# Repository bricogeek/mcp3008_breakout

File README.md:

MCP3008 Breakout Board
================

This MCP3008 breakout board will add 8 channels of 10-bit analog input to your microcontroller or microcomputer project and uses SPI so only 4 pins are required.

[   
*MCP3008 Breakout Board (BGK-0001)*](http://tienda.bricogeek.com/bricogeek/678-conversor-adc-8-bits-mcp3008.html)

License Information
-------------------
The hardware is released under [Creative Commons ShareAlike 4.0 International](https://creativecommons.org/licenses/by-sa/4.0/).

Distributed as-is; no warranty is given.

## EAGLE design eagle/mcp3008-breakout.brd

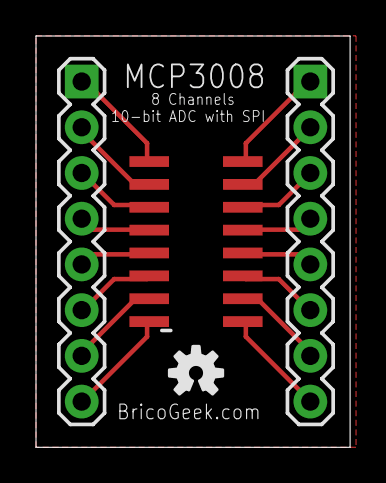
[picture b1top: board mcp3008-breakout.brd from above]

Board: 2 copper layers, 17.4 x 22.9 mm, 4 parts (0 on the bottom side), 15 nets.

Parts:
JP1, JP2: 1X08
U1: MCP3008; SOIC16N
U$2: OSHW-LOGO-S

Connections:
CH0: JP1.1, U1.1
CH1: JP1.2, U1.2
CH2: JP1.3, U1.3
CH3: JP1.4, U1.4
CH4: JP1.5, U1.5
CH5: JP1.6, U1.6
CH6: JP1.7, U1.7
CH7: JP1.8, U1.8
CLK: JP2.4, U1.13
CS: JP2.7, U1.10
DIN: JP2.6, U1.11
DOUT: JP2.5, U1.12
GND: JP2.3, JP2.8, U1.9, U1.14
VCC: JP2.1, U1.16
VREF: JP2.2, U1.15

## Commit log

2014-10-13 Readme update
2014-10-13 Added schematic and board layout
2014-10-13 Added board dimensions
2014-10-13 Quitados los nombres de los componentes en tValues
2014-10-13 Schematic
2014-10-31 Added MCP3008 datasheet
2014-10-31 Added product picture
2014-10-31 Readme info

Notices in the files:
parts and their libraries:
SparkFun-Connectors: Licensing: Creative Commons ShareAlike 4.0 International - https://creativecommons.org/licenses/by-sa/4.0
